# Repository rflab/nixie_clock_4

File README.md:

nixie_clock_3
=============

三代目ニキシー管時計

ソースコードと回路図、Atmel AVR ATMEGA328使用

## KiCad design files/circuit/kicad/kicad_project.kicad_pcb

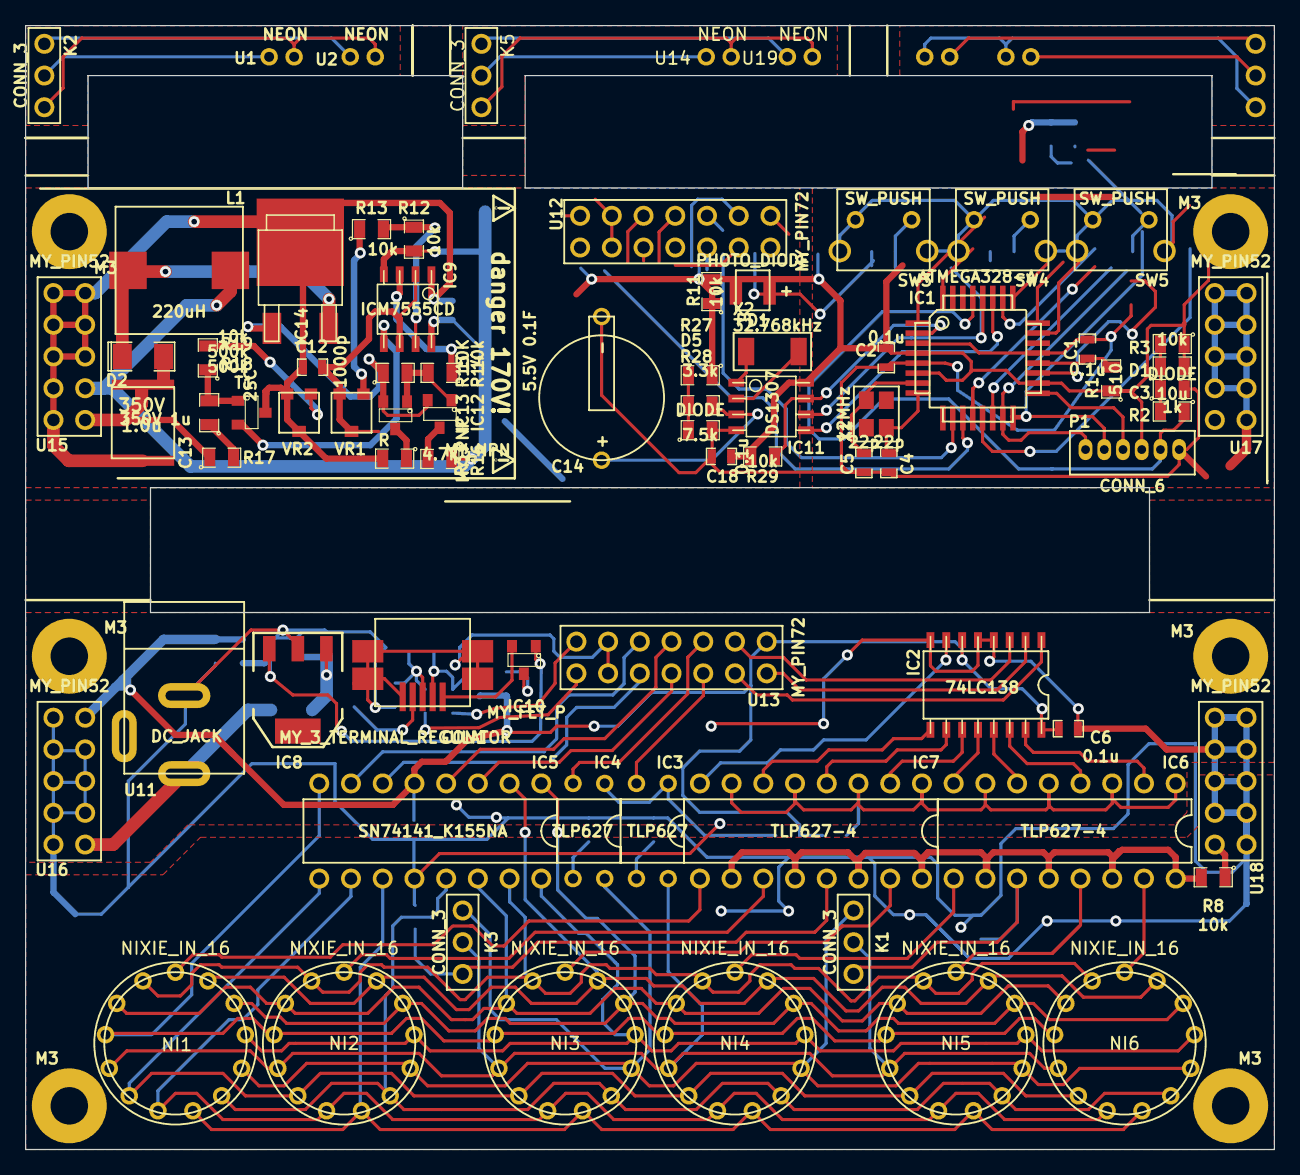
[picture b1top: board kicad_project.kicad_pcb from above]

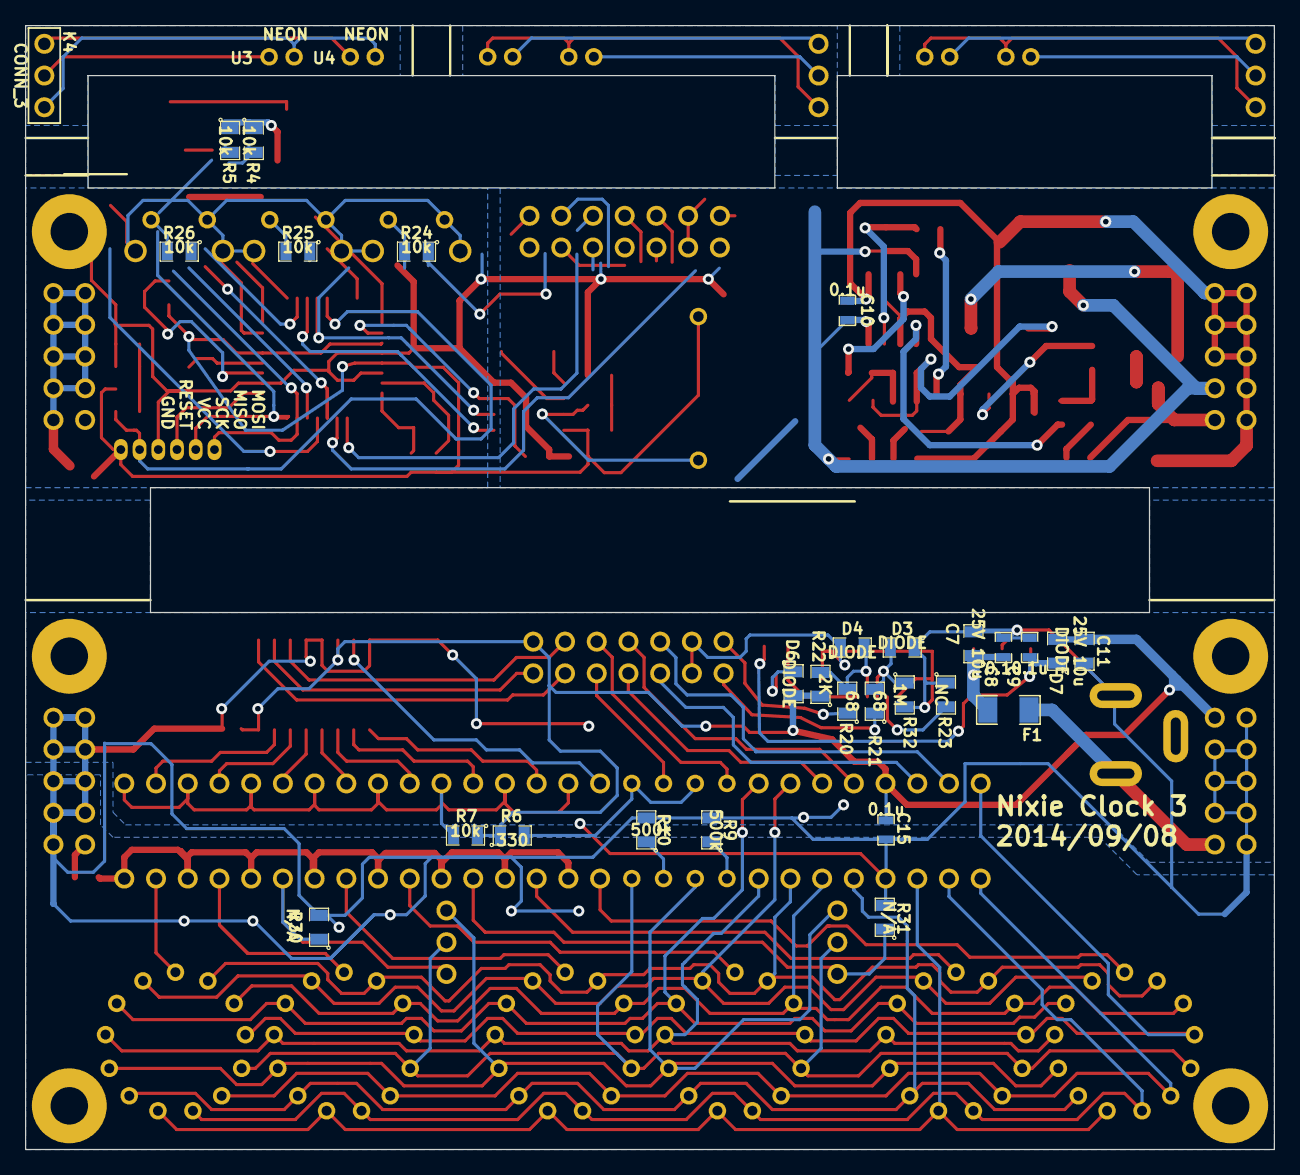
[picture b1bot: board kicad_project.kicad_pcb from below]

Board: 2 copper layers, 100.0 x 90.0 mm, 110 parts (30 on the bottom side), 109 nets.

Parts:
C1, C2, C6, C8, C9, C10, C15, C18: 0.1u; SM0603_Capa
C3: 10u; SM0805
C4, C5: 22p; SM0603_Capa
C7, C11: 25V 10u; SM0805
C12: 1000p; SM0603_Capa
C13: 350V 1u; my_SMD5750
C14: 5.5V 0.1F; my_double_layer_capacitor
CON1: USB_MINI_B; my_usb_mini_b
D1, D3, D4, D5, D6, D7: DIODE; SM0805
D2: DIODE; SM1206POL
F1: FUSE; SM1206
IC1: ATMEGA328-A; TQFP32
IC2: 74LC138; my_so16
IC3, IC4: TLP627; my_dip4
IC5: SN74141_K155NA; my_dip16
IC6, IC7: TLP627-4; my_dip16
IC8: MY_3_TERMINAL_REGULATOR; my_SOT223
IC9: ICM7555CD; so-8
IC10: MY_FET_P; my_SOT23
IC11: DS1307; so-8
IC12: MY_NPN; my_SOT23
IC13: MY_PNP; my_SOT23
IC14: MY_FET_N; my_sot428
K1, K2, K3, K4, K5: CONN_3; my_3pin
L1: 220uH; my_inductor
M3, M3#2, M3#3: my_M3_screw
NI1, NI2, NI3, NI4, NI5, NI6: NIXIE_IN_16; my_nixie
P1: CONN_6; my_connector_6
PD1: PHOTO_DIODE; my_photo_diode
R1: 510; SM0805
R2: 1k; SM0805
R3, R4, R5, R7, R8, R11, R12, R13, R14, R19, R24, R25, R26, R29: 10k; SM0805
R6: 330; SM0805
R9, R10, R17, R18: 500k; SM0805
R15: 10K; SM0805
R16: 4.7k; SM0805
R20, R21: 68; SM0805
R22: 2K; SM0805
R23: NC; SM0805
R27: 3.3k; SM0805
R28: 7.5k; SM0805
R30, R31: N/A; SM0805
R32: 1M; SM0805
R33: R; SM0805
SW3, SW4, SW5: SW_PUSH; my_tact_switch
T1: 2SC; SOT23
U1, U2, U3, U4, U14, U19: NEON; my_neon
U11: DC_JACK; my_dcjack
U12, U13: MY_PIN72; my_pin72
U15, U16, U17, U18: MY_PIN52; my_pin52
VR1: 100k; my_SMD_VR
VR2: 10k; my_SMD_VR
X1: 12MHz; my_crystal
X2: 32.768kHz; my_crystal_32p768

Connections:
170V: C13.1, D2.2, R17.1, U15.6
+5V: C6.2, C11.1, C15.1, D6.2, D7.2, IC2.6, IC2.16, IC5.5, R6.1, R7.1, R22.1, U13.8, U16.10
+9V: F1.1, U11.1, U16.6
/INT0_D+: IC1.32, U12.1
/INT1_D-: IC1.1, U12.14
/MISO: IC1.16, P1.5, U12.10
/MOSI: IC1.15, P1.6, U12.5
/PB0: IC1.12, U12.6
/PB1: IC1.13, U12.7
/PB2: IC1.14, U12.9
/PC0: IC1.23, U12.11
/PC1: IC1.24, U12.3
/PC2: IC1.25, U12.12
/PC3: IC1.26, U12.4
/PINPB0: IC2.1, U13.6
/PINPB1: IC2.2, U13.7
/PINPB2: IC2.3, U13.9
/PINPB3: IC3.2, U13.5
/PINPB4: IC4.2, U13.10
/PINPC0: IC5.7, U13.12
/PINPC1: IC5.6, U13.3
/PINPC2: IC5.4, U13.11
/PINPC3: IC5.3, U13.4
/RESET: IC1.29, P1.2, R2.1
/SCK: IC1.17, P1.4
/Sheet53F8BA4D/out: IC1.19, PD1.2, R11.2
/Sheet53F8FD69/A: IC1.11, R24.2, SW3.1
/Sheet53F8FD69/B: IC1.10, R25.2, SW4.1
/Sheet53F8FD69/Push: IC1.9, R26.2, SW5.1
/Sheet53F905A8/CLKOUT: IC1.2, IC11.7, R29.2
/Sheet53F905A8/SCL: IC1.28, IC11.6, R4.2
/Sheet53F905A8/SDA: IC1.27, IC11.5, R5.2
/nixie/L1: IC2.15, IC6.2
/nixie/L2: IC2.14, IC6.4
/nixie/L3: IC2.13, IC6.6
/nixie/L4: IC2.12, IC6.8
/nixie/L5: IC2.11, IC7.2
/nixie/L6: IC2.10, IC7.4
/nixie/L7: IC2.9, IC7.6
/nixie/L8: IC2.7, IC7.8
/nixie/N0: IC5.15, NI1.2, NI2.2, NI3.2, NI4.2, NI5.2, NI6.2
/nixie/N1: IC5.14, NI1.3, NI2.3, NI3.3, NI4.3, NI5.3, NI6.3
/nixie/N2: IC5.8, NI1.4, NI2.4, NI3.4, NI4.4, NI5.4, NI6.4
/nixie/N3: IC5.9, NI1.6, NI2.6, NI3.6, NI4.6, NI5.6, NI6.6
/nixie/N4: IC5.10, NI1.7, NI2.7, NI3.7, NI4.7, NI5.7, NI6.7
/nixie/N5: IC5.11, NI1.8, NI2.8, NI3.8, NI4.8, NI5.8, NI6.8
/nixie/N6: IC5.13, NI1.9, NI2.9, NI3.9, NI4.9, NI5.9, NI6.9
/nixie/N7: IC5.16, NI1.11, NI2.11, NI3.11, NI4.11, NI5.11, NI6.11
/nixie/N8: IC5.1, NI1.12, NI2.12, NI3.12, NI4.12, NI5.12, NI6.12
/nixie/N9: IC5.2, NI1.13, NI2.13, NI3.13, NI4.13, NI5.13, NI6.13
/nixie/Sheet53F9F7BA/1: IC6.15, NI6.1
/nixie/Sheet53F9F7BA/2: IC6.13, NI5.1
/nixie/Sheet53F9F7BA/3: IC6.9, NI4.1
/nixie/Sheet53F9F7BA/4: IC7.15, NI3.1
/nixie/Sheet53F9F7BA/5: IC7.11, NI2.1
/nixie/Sheet53F9F7BA/6: IC7.9, NI1.1
/nixie/Sheet53F9F7BA/NEG1: K2.1, U1.2, U2.2
/nixie/Sheet53F9F7BA/NEG2: K4.1, U3.2, U4.2
/nixie/Sheet53F9F7BA/NEG3: K5.1, U14.2, U19.2
/nixie/Sheet53F9F7BA/NEL1: K2.2, U1.1
/nixie/Sheet53F9F7BA/NEL2: K4.2, U3.1
/nixie/Sheet53F9F7BA/NEL3: K5.2, U14.1
/nixie/Sheet53F9F7BA/NEU1: K2.3, U2.1
/nixie/Sheet53F9F7BA/NEU2: K4.3, U4.1
/nixie/Sheet53F9F7BA/NEU3: K5.3, U19.1
/nixie/Sheet53F9F7BA/colon_l: IC6.11, K1.1, R30.1
/nixie/Sheet53F9F7BA/colon_r: IC7.13, K3.1, R31.1
/nixie/Sheet53F9F7BA/dot_cathode_l: IC3.4, K1.2, K3.2, NI1.5, NI2.5, NI3.5, NI4.5, NI5.5, NI6.5
/nixie/Sheet53F9F7BA/dot_cathode_r: IC4.4, K1.3, K3.3, NI1.10, NI2.10, NI3.10, NI4.10, NI5.10, NI6.10
GND: C6.1, C7.2, C8.2, C9.2, C11.2, C15.2, CON1.5, CON1.6, CON1.7, CON1.8, CON1.9, D3.1, D4.1, IC2.4, IC2.5, IC2.8, IC5.12, IC8.2, R9.2, R10.2, R23.1, R30.2, R31.2, R32.2, U11.3, U13.2, U13.13, U16.1, U16.2, U16.3, U16.4, U16.5, U16.7, U16.8, U16.9, U18.1, U18.2, U18.3, U18.4, U18.6, U18.7, U18.8, U18.9, U18.10
unnamed: C1.1, IC1.20, R1.2
unnamed: C5.1, IC1.7, X1.2
unnamed: C4.1, IC1.8, X1.1
unnamed: C3.1, D1.1, R2.2, R3.2
unnamed: IC3.1, IC4.1, R6.2
unnamed: IC4.3, R9.1
unnamed: IC3.3, R10.1
unnamed: IC6.1, IC6.3, IC6.5, IC6.7, IC7.1, IC7.3, IC7.5, IC7.7, R7.2
unnamed: IC6.10, IC6.12, IC6.14, IC6.16, IC7.10, IC7.12, IC7.14, IC7.16, R8.2
unnamed: C12.1, IC9.2, IC9.6, VR1.2, VR1.3
unnamed: R13.1, VR1.1
unnamed: R19.2, VR2.1
unnamed: R17.2, R18.1
unnamed: D2.1, IC14.3, L1.2
unnamed: IC12.3, R16.2
unnamed: IC12.2, IC13.2, IC14.1, R15.1
unnamed: IC12.1, IC13.1, R14.2, R15.2
unnamed: IC9.7, R12.1, R13.2
unnamed: IC9.5, T1.2
unnamed: C7.1, C8.1, F1.2, IC8.1
unnamed: R18.2, R19.1, T1.1
unnamed: D6.1, IC10.3
unnamed: IC13.3, R33.1
unnamed: C9.1, D7.1, IC8.3, IC10.1
unnamed: IC9.3, R14.1
unnamed: CON1.4, R23.2
unnamed: CON1.3, D3.2, R21.2, R32.1
unnamed: CON1.2, D4.2, R20.2, R22.2
unnamed: D5.1, R27.2, R28.1
unnamed: C14.1, D5.2, IC11.3
unnamed: IC11.1, X2.2
unnamed: IC11.2, X2.1
PIN5V: C2.1, C18.1, D1.2, IC1.4, IC1.6, IC1.18, IC11.8, P1.3, PD1.1, R1.1, R3.1, R4.1, R5.1, R24.1, R25.1, R26.1, R27.1, R29.1, U12.8, U17.5
PIN9V: C10.2, IC9.4, IC9.8, L1.1, R12.2, R16.1, U15.7
PIN170V: R8.1, U18.5
PIND+: R21.1, U13.1
PIND-: R20.1, U13.14
PINGND: C1.2, C2.2, C3.2, C4.2, C5.2, C10.1, C12.2, C13.2, C14.2, C18.2, IC1.3, IC1.5, IC1.21, IC9.1, IC11.4, IC14.2, P1.1, R11.1, R28.2, R33.2, SW3.2, SW4.2, SW5.2, T1.3, U12.2, U12.13, U15.1, U15.2, U15.3, U15.4, U15.5, U15.8, U15.9, U15.10, U17.1, U17.2, U17.3, U17.4, U17.6, U17.7, U17.8, U17.9, U17.10, VR2.2, VR2.3
USB5V: CON1.1, IC10.2

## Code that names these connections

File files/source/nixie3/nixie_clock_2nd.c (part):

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#define PIN_DIGIT_3 RB0
#define PIN_DIGIT_4 RC6
#define PIN_DIGIT_5 RC5
#define PIN_COLON_L RB2
#define PIN_COLON_R RC7
#define PIN_TEMPARATURE_SENSOR RA0
#define PIN_CDS RA1
#define PIN_TRANSISTOR_0 RA2
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			PIN_DIGIT_3 = 0;
			PIN_DIGIT_4 = 0;
			PIN_DIGIT_5 = 0;
			PIN_COLON_L = 0;
			PIN_COLON_R = 0;
			break;
		case DIGIT_0:
			PIN_DIGIT_0 = 1;
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			PIN_DIGIT_3 = 0;
			PIN_DIGIT_4 = 0;
			PIN_DIGIT_5 = 0;
			PIN_COLON_L = 0;
			PIN_COLON_R = 0;
			break;
		case DIGIT_1:
			PIN_DIGIT_0 = 0;
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			PIN_DIGIT_3 = 0;
			PIN_DIGIT_4 = 0;
			PIN_DIGIT_5 = 0;
			PIN_COLON_L = 0;
			PIN_COLON_R = 0;
			break;
		case DIGIT_2:
			PIN_DIGIT_0 = 0;
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			PIN_DIGIT_3 = 0;
			PIN_DIGIT_4 = 0;
			PIN_DIGIT_5 = 0;
			PIN_COLON_L = 0;
			PIN_COLON_R = 0;
			break;
		case DIGIT_3:
			PIN_DIGIT_0 = 0;
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			PIN_DIGIT_3 = 1;
			PIN_DIGIT_4 = 0;
			PIN_DIGIT_5 = 0;
			PIN_COLON_L = 0;
			PIN_COLON_R = 0;
			break;
		case DIGIT_4:
			PIN_DIGIT_0 = 0;
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			PIN_DIGIT_3 = 0;
			PIN_DIGIT_4 = 1;
			PIN_DIGIT_5 = 0;
			PIN_COLON_L = 0;
			PIN_COLON_R = 0;
			break;
		case DIGIT_5:
			PIN_DIGIT_0 = 0;
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			PIN_DIGIT_3 = 0;
			PIN_DIGIT_4 = 0;
			PIN_DIGIT_5 = 1;
			PIN_COLON_L = 0;
			PIN_COLON_R = 0;
			break;
		case DIGIT_COLON_L:
			PIN_DIGIT_0 = 0;
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			PIN_DIGIT_3 = 0;
			PIN_DIGIT_4 = 0;
			PIN_DIGIT_5 = 0;
			PIN_COLON_L = 1;
			PIN_COLON_R = 0;
			break;
		case DIGIT_COLON_R:
			PIN_DIGIT_0 = 0;
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			PIN_DIGIT_3 = 0;
			PIN_DIGIT_4 = 0;
			PIN_DIGIT_5 = 0;
			PIN_COLON_L = 0;
			PIN_COLON_R = 1;
			break;
		default:
			;
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{
	static unsigned char state = 0;
	static unsigned char prev_press = 1;
	unsigned char push = 0;
	g_disp_flag = 0b11111111;

	if (PIN_BUTTON_2 == 0)
	{
		if (prev_press == 0)
		{
			push = 1;
		}
		else
		{
			push = 0;
		}
		prev_press = 1;
	}
	else
	{
		push = 0;
		prev_press = 0;
	}

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{
	static unsigned char state = 0;
	static unsigned char prev_press = 1;
	unsigned char push = 0;
	g_disp_flag = 0b11111111;

	if (PIN_BUTTON_2 == 0)
	{
		if (prev_press == 0)
		{
			push = 1;
		}
		else
		{
			push = 0;
		}
		prev_press = 1;
	}
	else
	{
		push = 0;
		prev_press = 0;
	}

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{
	static unsigned char state = 0;
	static unsigned char prev_press = 1;
	unsigned char push = 1;
	g_disp_flag = 0b11111100;

	if (PIN_BUTTON_2 == 0)
	{
		if (prev_press == 0)
		{
			push = 1;
		}
		else
		{
			push = 0;
		}
		prev_press = 1;
	}
	else
	{
		push = 0;
		prev_press = 0;
	}

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{
	static unsigned char state = 0;
	static unsigned char prev_press = 1;
	unsigned char push = 0;
	g_disp_flag = 0b11111111;

	if (PIN_BUTTON_2 == 0)
	{
		if (prev_press == 0)
		{
			push = 1;
		}
		else
		{
			push = 0;
		}
		prev_press = 1;
	}
	else
	{
		push = 0;
		prev_press = 0;
	}
	
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
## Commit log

2015-03-21 :confetti_ball: Added .gitattributes & .gitignore files
2015-03-21 add files

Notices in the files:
files/source/nixie3/nixie_clock_2nd.c:
Rf Lab. all rights reserved.
